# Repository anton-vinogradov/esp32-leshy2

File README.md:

<div align="center">

# Leshy2 ⭐

### An open standalone pocket tool for radio, communication and authorised research

**2.4/5-GHz Wi‑Fi · BLE · 802.15.4 · 3× nRF24 · Sub‑GHz · VHF/UHF · FM/AM/SW/LW/Airband · IR · LoRa/CC1101+NFC Cap**

[Capabilities](docs/hardware.md) · [Roadmap](docs/roadmap.md) · [Stage reports](docs/stage-results.md) · [Schematics](docs/schematics.md) · [Firmware](https://github.com/anton-vinogradov/esp32-leshy2-firmware) · [Русский](README.ru.md)

</div>

<!-- current-substep: H6.0.3-R1 -->

## What we want

Leshy2 is intended to be a hobby device combining spectrum
observation, communication, diagnostics and safe experimentation without a
mandatory laptop. The first order targets one genuinely working prototype:
the factory supplies two populated PCBAs and the owner completes a simple,
solder-free final assembly.

Repairability is not a design priority and does not justify greater cost, size,
or layout/manufacturing complexity. Optional service conveniences are acceptable
only without those penalties. Safety, reliability, required assembly and test
access, and firmware programming/recovery remain mandatory.

PCB layer count is an engineering choice based on electrical integrity,
manufacturability and the complete quoted cost, not a minimization target.
The current six-layer baseline is retained until a validated comparison justifies a change.

| Area | Intended result |
|---|---|
| Radio | S3 Wi‑Fi/BLE, C5 2.4/5-GHz Wi‑Fi and 802.15.4, 3× full nRF24, CC1101, VHF/UHF voice, FM/AM/SW/LW/Airband RX and IR |
| Interface | 3.5-inch 320×480 touch IPS, direct i8080‑8, buttons, encoder, microSD and audio |
| Expansion | Protected Cap slot for U214 LoRa or U219 CC1101+NFC and an M5 Unit port |
| Reliability | Four independent USB ports, accessible recovery, hardware TX evidence and fail-closed safety |

Transmission and hazardous laboratory functions are constrained by the
[safety model](docs/safety.md); the device is only for lawful use with the
system owner's permission.

## What we decided

- Two 80 × 150-mm six-layer boards: front UI/radio and rear RF/power.
- Six compute domains: S3, C5, front Hub RP, rear RF RP, Pack and Safety.
- Ten permanent antenna ports are split 5+5; each RF path remains board-local and reaches its external connector directly or through one removable microcoax.
- The EastRising `ER-TFT035IPS-6 + ER-TPC035-6` display connects directly to S3 through a 50-contact ZIF and i8080‑8; its FPC points toward the antenna edge, folds without twist and retains at least 5 mm of relaxed reserve.
- The factory fabricates and populates two PCBAs. Without soldering, the owner fits the display on a stock rectangular PSA pad, five microcoax jumpers, knob, fasteners and enclosure.
- The 80-contact M1 carries no structural load; four nylon screws, compression stops and the enclosure carry it.
- The 80 × 150-mm outline remains while routing meets its rules. If a required power, USB/i8080 or RF path cannot route after legal local rearrangement, the next candidate is 85 × 150 mm followed by complete requalification.

## What is designed

### Physical layout

The current preview below is composed from the actual PCBs: exterior faces share one scale, without an extra rear-board mirror. Only the installed display panel's envelope is added in blue. This is not an assembled 3D validation. Inspect the inner sides in [all four current component views](docs/h6-r2-component-views.md). Coordinates and cable paths are available in the [exact-placement](docs/h6-r2-exact-placement.md) and [microcoax](docs/h6-r2-microcoax-service.md) views.

H1-to-native correspondence is not fully verified: H1 remains a concept archive, not a picture of current positions. [H6 corrections and open interface findings](docs/h6-r2-interface-review.md) describe the current boards.

[Placement corrections and their verification](docs/h6-r2-placement-repair.md) explain the holder, encoder, port/card access and internal audio assembly. The routing phase is still open.

[Component unification](docs/h6-r2-component-unification.md): GCT USB4105-GF-A ×4 is installed on the native boards; fresh DRC/parity and preservation checks pass. Other candidates and necessary functional differences remain separate.

[Archive: H1 concept four-face Leshy2 mock-up](docs/images/h1-r2-four-faces.svg?rev=h1-r2.39-views-20260907)

[Legend for 223 H1 concept bodies](docs/images/h1-r2-component-legend.svg?rev=h1-r2.39-views-20260907) ·
[physical-design report](docs/h1-r2-physical-layout.md) ·
[functional-architecture report](docs/h0-r2-functional-architecture.md) ·
[front inner face](docs/images/h1-r2-inner-ui.svg) ·
[rear inner face](docs/images/h1-r2-inner-rf.svg) ·
[display mounting](docs/images/display-mount.svg) ·
[physical sections](docs/images/h1-r2-inner-sections.svg)

### Current routing

These are exports from the live `.kicad_pcb` files, not illustrative mock-ups.
Open either board for the full-size SVG.

<table>
  <tr>
    <td width="50%"></td>
    <td width="50%"></td>
  </tr>
  <tr><td align="center">UI PCB</td><td align="center">RF / power PCB</td></tr>
</table>

### Current components · both faces

All four views use the same scale. Outer faces are above; inner faces below
are viewed after turning each board over, with the antenna edge still at the top.
Grey shows component outlines/references; blue is actual silkscreen.
Known footprint defects remain visible — these views do not certify assembly.
[Full-size views and legend](docs/h6-r2-component-views.md). Gold shows all 50 SMA lands and the two-sided copper lands of USB, Cap and encoder interfaces; NFC endpoints are distinguished in the legend.

[Interface labels and coverage](docs/h6-r2-interface-silkscreen.md) distinguish user, service and assembly silkscreen from grey drawing references.

<table>
  <tr><th width="50%">Front / UI</th><th width="50%">Rear / RF-power</th></tr>
  <tr>
    <td></td>
    <td></td>
  </tr>
  <tr>
    <td></td>
    <td></td>
  </tr>
</table>

Component views refresh together with routing exports; the common freshness
check rejects images that no longer match the PCB files.

## What we obtained and verified

**Current hardware marker: `H6.0.3-R1`.**

- The historical H0–H5 reviews, including H2 native production ECAD, retain their own baseline scope; their reports are collected in [one index](docs/stage-results.md).
- **Current H3 is `review_required`.** The [current analytical result](docs/h3-r2-acceptance.md) and [rail-voltage paths](docs/power-rail-margins.md) now use the fitted MAIN converter/divider/current-setting resistor. They expose current and voltage shortfalls; MAIN temperature is not established. The MAIN/AON circuit remains unqualified for production or battery energization.
- Both native KiCad boards pass the current [exact-placement checks](docs/h6-r2-exact-placement.md).
- Manufacturer-drawing corrections are being integrated into both PCBs. The [native interface review](docs/h6-r2-interface-review.md) separates applied corrections from remaining assembly gates; clean DRC alone does not prove physical assembly.
- Recovery: S3 ROM UART0 has dedicated native pins; the [C5 TS3/LV control correction](docs/h6-r2-c5-mux-control-review.md) is implemented in source/native ECAD with scoped topology and DRC/parity checks passed. The Safety service manager, electrical/HIL qualification and KILL/update policy remain open; LV20 requires Pre-order, MOQ 21. [Actual recovery boundary](docs/service-recovery.md).
- [Routing automation and design checks](docs/h6-r2-routing-automation.md): the benchmark passed **474/474 connections plus three identical cold replays per block**; the new parallel acceptance command reports current design blockers explicitly. Production routing remains paused pending full-board and electrical qualification. Live copper/connectivity counts, hash-bound DRC results and electrical-review limitations have one owner: [H6.0.3-R1](docs/h6-r2-current-routing.md).
- Native ERC currently uses passive symbol pins; zero findings do not prove correct rail sources or compatible outputs. This electrical-semantics gap blocks release; [corrected pin mappings and partial typed-ERC review](docs/h6-r2-electrical-semantics.md) describe the current evidence and remaining work.

## What remains

1. Correct the native interface/assembly findings and close the electrical-pin/rail-source review gap, then finish every connection and zero schematic-to-PCB parity in H6.0.3.
2. Re-run power/thermal, USB/i8080/M1, RF/Airband, plane and return-current checks on the actual copper.
3. Check STEP, enclosure, cables and final assembly; produce Gerber/BOM/CPL and complete independent DFM/CPL review.
4. Build the first-spin firmware package: reproducible images, fake HAL, available emulation, display test patterns and a safe first-power-on procedure.
5. Immediately before ordering, recheck every exact MPN against JLCPCB Standard PCBA stock/MOQ/price and approve the single actual quote.

Ordering and fabrication remain blocked.

## How the documentation is organised

Each kind of information now has one owner so the same decision is not retold
on several pages:

| Document | Sole role |
|---|---|
| This page | Product story: intent → decisions → implementation → result → remaining work |
| [Roadmap](docs/roadmap.md) | Stage order, current marker and transition criteria only |
| [Stage reports](docs/stage-results.md) | Links to immutable completed-phase results only |
| [Physical design](docs/h1-r2-physical-layout.md), [schematics](docs/schematics.md), [cost](docs/h1-r2-cost.md) | Detail for one subject area |
| `hardware/**/generated` and release contracts | Machine-checkable truth |

Navigation links may repeat; substantive claims belong to their one owner. The
English pages are translations of the Russian pages with the same structure,
not a second independent narrative.

Licensed under [CERN Open Hardware Licence Version 2 — Strongly Reciprocal](LICENSE).

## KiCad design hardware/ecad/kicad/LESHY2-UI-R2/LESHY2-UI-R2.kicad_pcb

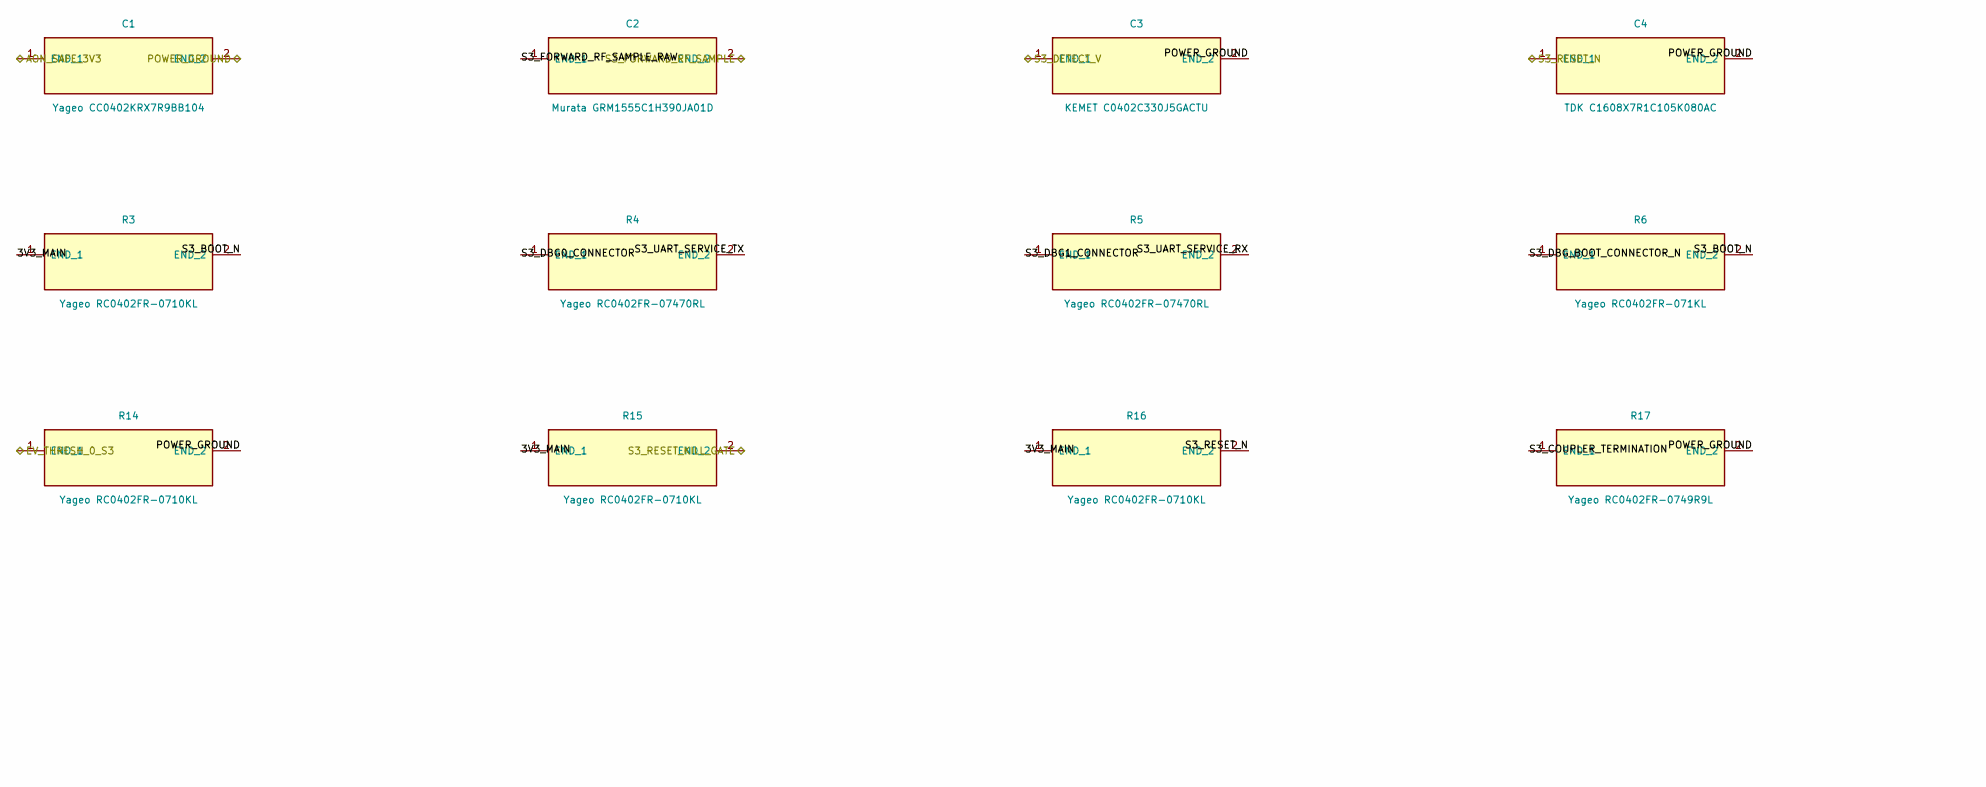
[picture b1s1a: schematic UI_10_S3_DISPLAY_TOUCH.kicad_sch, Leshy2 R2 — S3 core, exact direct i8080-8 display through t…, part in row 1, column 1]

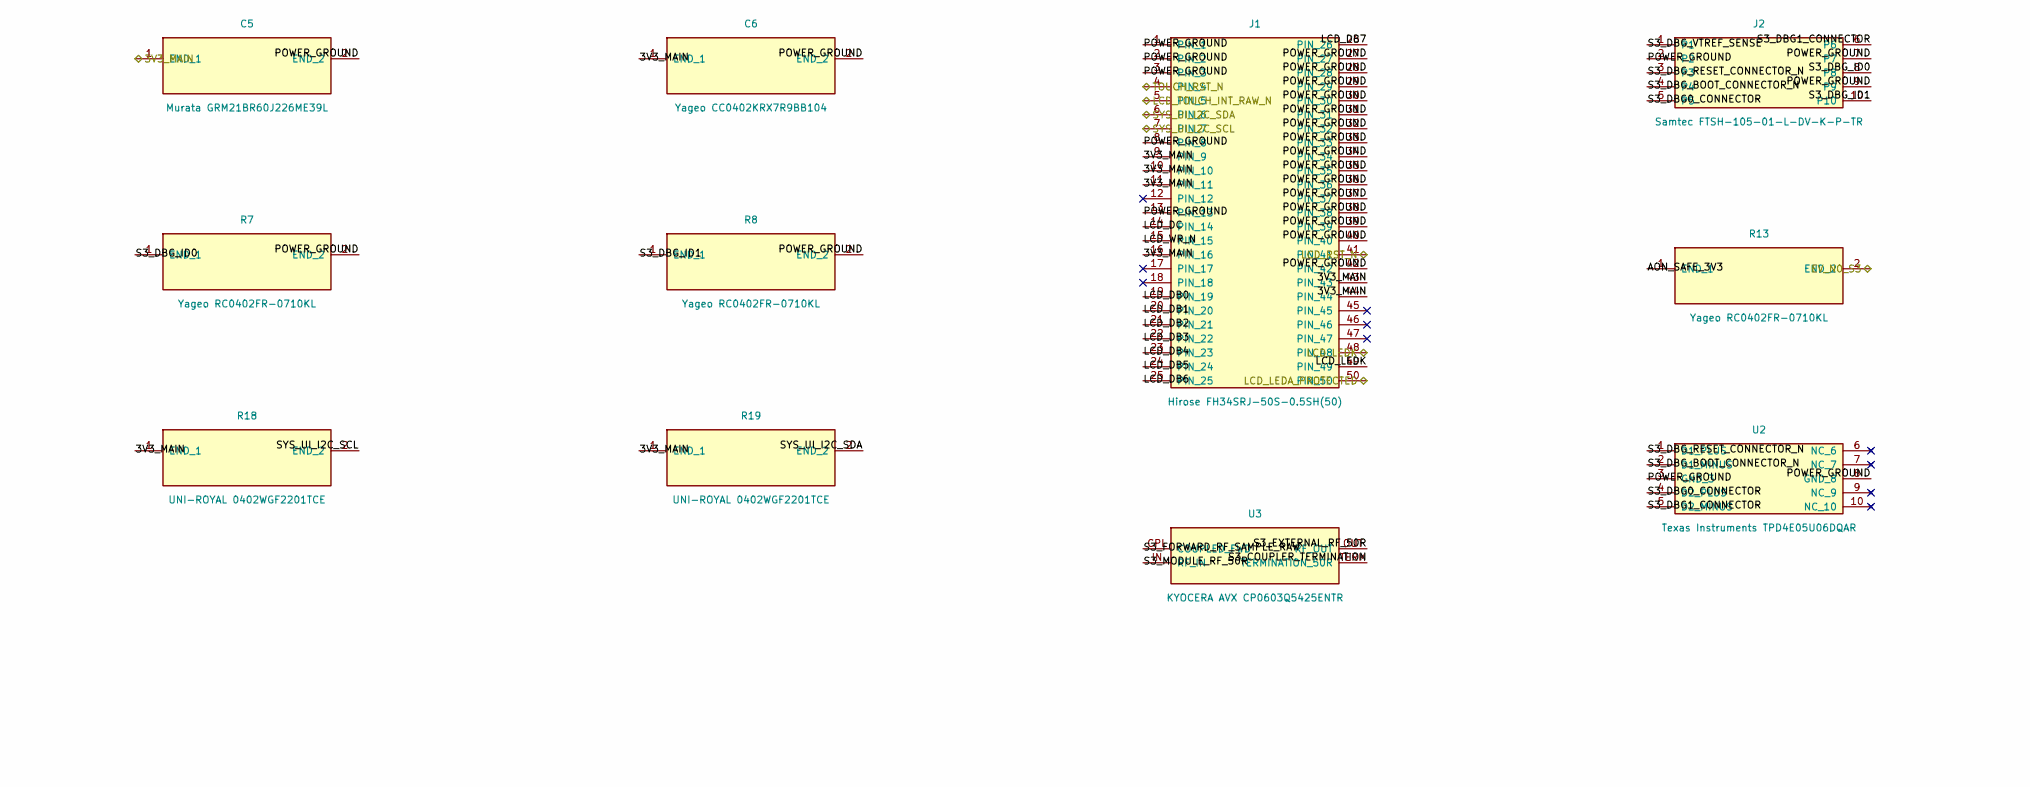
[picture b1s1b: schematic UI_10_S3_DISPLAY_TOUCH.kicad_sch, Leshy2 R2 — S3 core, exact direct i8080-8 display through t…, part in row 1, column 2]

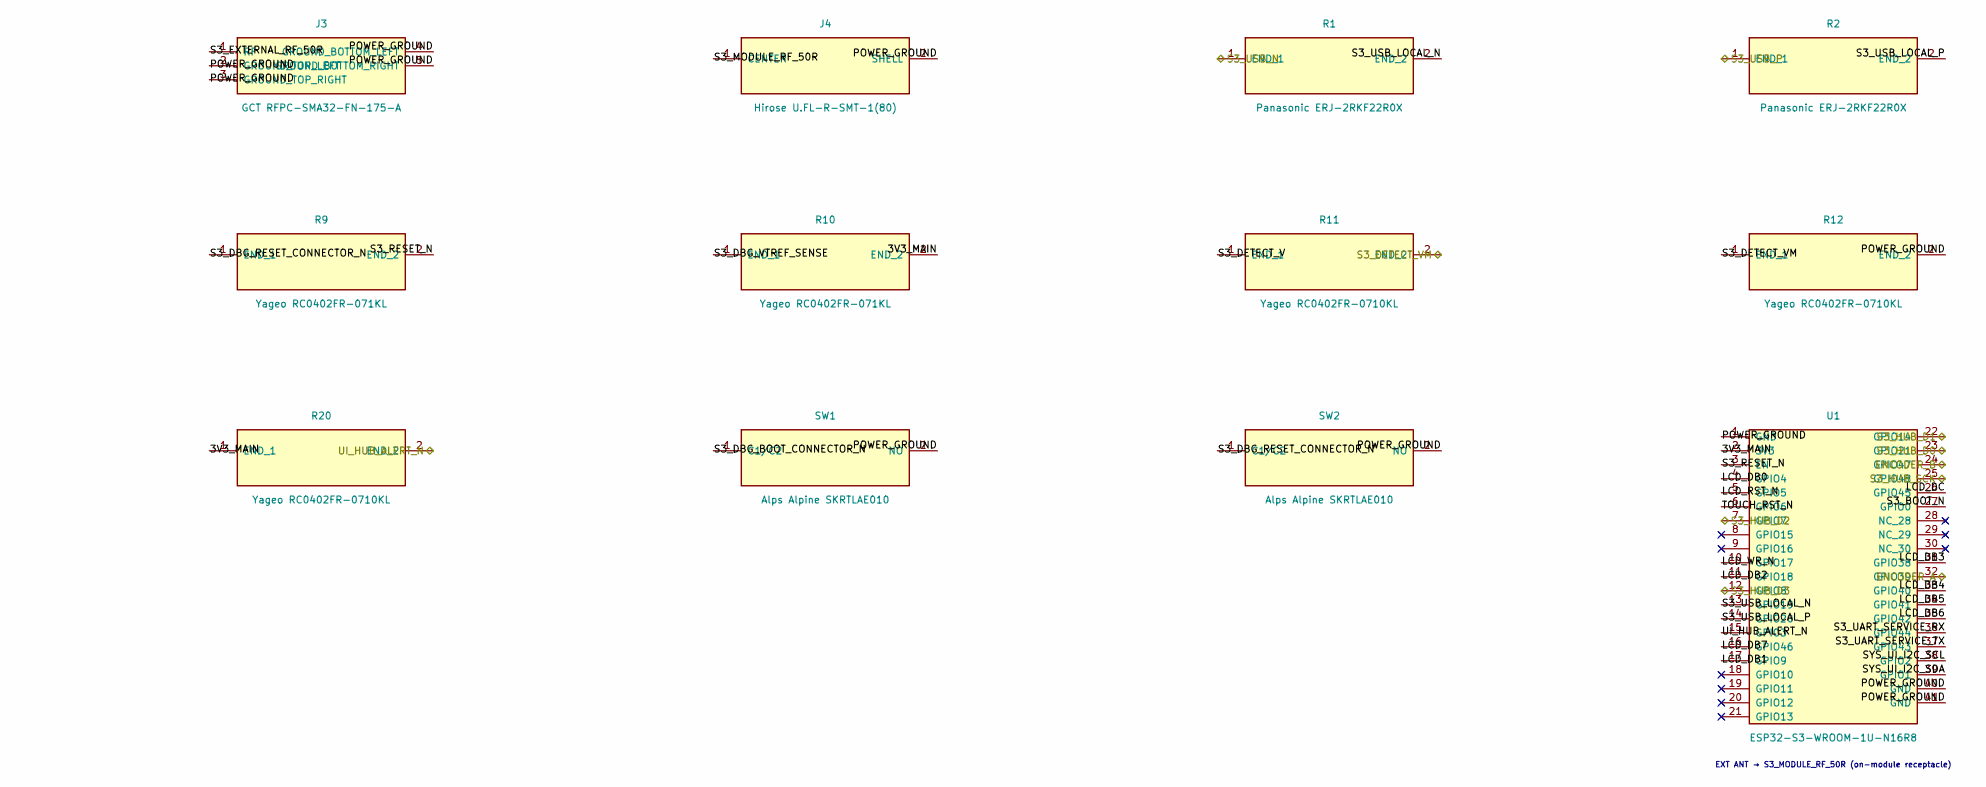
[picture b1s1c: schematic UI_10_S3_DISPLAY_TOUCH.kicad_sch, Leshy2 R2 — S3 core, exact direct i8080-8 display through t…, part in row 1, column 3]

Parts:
C1, C6: Yageo CC0402KRX7R9BB104; C_0402_1005Metric
C2: Murata GRM1555C1H390JA01D; C_0402_1005Metric
C3: KEMET C0402C330J5GACTU; C_0402_1005Metric
C4: TDK C1608X7R1C105K080AC; C_0603_1608Metric
C5: Murata GRM21BR60J226ME39L; C_0805_2012Metric
J1: Hirose FH34SRJ-50S-0.5SH(50); FH34SRJ-50S-0.5SH-50
J2: Samtec FTSH-105-01-L-DV-K-P-TR; FTSH-105-01-L-DV-K-P-TR
J3: GCT RFPC-SMA32-FN-175-A; RFPC-SMA32-FN-175-A
J4: Hirose U.FL-R-SMT-1(80); U.FL_Hirose_U.FL-R-SMT-1_Vertical
R1, R2: Panasonic ERJ-2RKF22R0X; R_0402_1005Metric
R3, R7, R8, R11, R12, R13, R14, R15, R16, R20: Yageo RC0402FR-0710KL; R_0402_1005Metric
R4, R5: Yageo RC0402FR-07470RL; R_0402_1005Metric
R6, R9, R10: Yageo RC0402FR-071KL; R_0402_1005Metric
R17: Yageo RC0402FR-0749R9L; R_0402_1005Metric
R18, R19: UNI-ROYAL 0402WGF2201TCE; R_0402_1005Metric
SW1, SW2: Alps Alpine SKRTLAE010; SW_Push_1P1T-MP_NO_Horizontal_Alps_SKRTLAE010
U1: ESP32-S3-WROOM-1U-N16R8; ESP32-S3-WROOM-1U
U2: Texas Instruments TPD4E05U06DQAR; USON-10_2.5x1.0mm_P0.5mm
U3: KYOCERA AVX CP0603Q5425ENTR; CP0603Q5425ENTR

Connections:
/UI_10_S3_DISPLAY_TOUCH/3V3_MAIN: C5.1 (END_1), C6.1 (END_1), J1.9 (PIN_9), J1.10 (PIN_10), J1.11 (PIN_11), J1.16 (PIN_16), J1.43 (PIN_43), J1.44 (PIN_44), R3.1 (END_1), R10.2 (END_2), R15.1 (END_1), R16.1 (END_1), R18.1 (END_1), R19.1 (END_1), R20.1 (END_1), U1.2 (3V3); also elsewhere on the board
/UI_10_S3_DISPLAY_TOUCH/AON_SAFE_3V3: C1.1 (END_1), R13.1 (END_1); also elsewhere on the board
/UI_10_S3_DISPLAY_TOUCH/ENCODER_A: U1.32 (GPIO39); also elsewhere on the board
/UI_10_S3_DISPLAY_TOUCH/ENCODER_B: U1.24 (GPIO47); also elsewhere on the board
/UI_10_S3_DISPLAY_TOUCH/LCD_DB0: J1.19 (PIN_19), U1.4 (GPIO4)
/UI_10_S3_DISPLAY_TOUCH/LCD_DB1: J1.20 (PIN_20), U1.17 (GPIO9)
/UI_10_S3_DISPLAY_TOUCH/LCD_DB2: J1.21 (PIN_21), U1.11 (GPIO18)
/UI_10_S3_DISPLAY_TOUCH/LCD_DB3: J1.22 (PIN_22), U1.31 (GPIO38)
/UI_10_S3_DISPLAY_TOUCH/LCD_DB4: J1.23 (PIN_23), U1.33 (GPIO40)
/UI_10_S3_DISPLAY_TOUCH/LCD_DB5: J1.24 (PIN_24), U1.34 (GPIO41)
/UI_10_S3_DISPLAY_TOUCH/LCD_DB6: J1.25 (PIN_25), U1.35 (GPIO42)
/UI_10_S3_DISPLAY_TOUCH/LCD_DB7: J1.26 (PIN_26), U1.16 (GPIO46)
/UI_10_S3_DISPLAY_TOUCH/LCD_DC: J1.14 (PIN_14), U1.26 (GPIO45)
/UI_10_S3_DISPLAY_TOUCH/LCD_LEDK: J1.48 (PIN_48), J1.49 (PIN_49); also elsewhere on the board
/UI_10_S3_DISPLAY_TOUCH/LCD_RST_N: J1.41 (PIN_41), U1.5 (GPIO5); also elsewhere on the board
/UI_10_S3_DISPLAY_TOUCH/LCD_WR_N: J1.15 (PIN_15), U1.10 (GPIO17)
/UI_10_S3_DISPLAY_TOUCH/POWER_GROUND: C1.2 (END_2), C3.2 (END_2), C4.2 (END_2), C5.2 (END_2), C6.2 (END_2), J1.1 (PIN_1), J1.2 (PIN_2), J1.3 (PIN_3), J1.8 (PIN_8), J1.13 (PIN_13), J1.27 (PIN_27), J1.28 (PIN_28), J1.29 (PIN_29), J1.30 (PIN_30), J1.31 (PIN_31), J1.32 (PIN_32), J1.33 (PIN_33), J1.34 (PIN_34), J1.35 (PIN_35), J1.36 (PIN_36), J1.37 (PIN_37), J1.38 (PIN_38), J1.39 (PIN_39), J1.40 (PIN_40), J1.42 (PIN_42), J2.2, J2.7, J2.9, J3.2 (GROUND_TOP_LEFT), J3.3 (GROUND_TOP_RIGHT), J3.4 (GROUND_BOTTOM_LEFT), J3.5 (GROUND_BOTTOM_RIGHT), J4.2 (SHELL), R7.2 (END_2), R8.2 (END_2), R12.2 (END_2), R14.2 (END_2), R17.2 (END_2), SW1.2 (NO), SW2.2 (NO), U1.1 (GND), U1.40 (GND), U1.41 (GND), U2.3 (GND_3), U2.8 (GND_8); also elsewhere on the board
/UI_10_S3_DISPLAY_TOUCH/S3_BOOT_N: R3.2 (END_2), R6.2 (END_2), U1.27 (GPIO0)
/UI_10_S3_DISPLAY_TOUCH/S3_COUPLER_TERMINATION: R17.1 (END_1), U3.TERM (TERMINATION_50R)
/UI_10_S3_DISPLAY_TOUCH/S3_DBG0_CONNECTOR: J2.5, R4.1 (END_1), U2.4 (D2_PLUS)
/UI_10_S3_DISPLAY_TOUCH/S3_DBG1_CONNECTOR: J2.6, R5.1 (END_1), U2.5 (D2_MINUS)
/UI_10_S3_DISPLAY_TOUCH/S3_DBG_BOOT_CONNECTOR_N: J2.4, R6.1 (END_1), SW1.1 (C1/C2), U2.2 (D1_MINUS)
/UI_10_S3_DISPLAY_TOUCH/S3_DBG_ID0: J2.8, R7.1 (END_1)
/UI_10_S3_DISPLAY_TOUCH/S3_DBG_ID1: J2.10, R8.1 (END_1)
/UI_10_S3_DISPLAY_TOUCH/S3_DBG_RESET_CONNECTOR_N: J2.3, R9.1 (END_1), SW2.1 (C1/C2), U2.1 (D1_PLUS)
/UI_10_S3_DISPLAY_TOUCH/S3_DBG_VTREF_SENSE: J2.1, R10.1 (END_1)
/UI_10_S3_DISPLAY_TOUCH/S3_DETECT_V: C3.1 (END_1), R11.1 (END_1); also elsewhere on the board
/UI_10_S3_DISPLAY_TOUCH/S3_DETECT_VM: R11.2 (END_2), R12.1 (END_1); also elsewhere on the board
/UI_10_S3_DISPLAY_TOUCH/S3_EXTERNAL_RF_50R: J3.1 (RF), U3.OUT (RF_OUT)
/UI_10_S3_DISPLAY_TOUCH/S3_FORWARD_RF_SAMPLE: C2.2 (END_2); also elsewhere on the board
/UI_10_S3_DISPLAY_TOUCH/S3_FORWARD_RF_SAMPLE_RAW: C2.1 (END_1), U3.CPL (COUPLED_FWD)
/UI_10_S3_DISPLAY_TOUCH/S3_HUB_D0: U1.23 (GPIO21); also elsewhere on the board
/UI_10_S3_DISPLAY_TOUCH/S3_HUB_D1: U1.22 (GPIO14); also elsewhere on the board
/UI_10_S3_DISPLAY_TOUCH/S3_HUB_D2: U1.7 (GPIO7); also elsewhere on the board
/UI_10_S3_DISPLAY_TOUCH/S3_HUB_D3: U1.12 (GPIO8); also elsewhere on the board
/UI_10_S3_DISPLAY_TOUCH/S3_HUB_SCK: U1.25 (GPIO48); also elsewhere on the board
/UI_10_S3_DISPLAY_TOUCH/S3_MODULE_RF_50R: J4.1 (CENTER), U3.IN (RF_IN)
/UI_10_S3_DISPLAY_TOUCH/S3_RESET_KILL_GATE: R15.2 (END_2); also elsewhere on the board
/UI_10_S3_DISPLAY_TOUCH/S3_RESET_N: C4.1 (END_1), R9.2 (END_2), R16.2 (END_2), U1.3 (EN); also elsewhere on the board
/UI_10_S3_DISPLAY_TOUCH/S3_UART_SERVICE_RX: R5.2 (END_2), U1.36 (GPIO44)
/UI_10_S3_DISPLAY_TOUCH/S3_UART_SERVICE_TX: R4.2 (END_2), U1.37 (GPIO43)
/UI_10_S3_DISPLAY_TOUCH/S3_USB_LOCAL_N: R1.2 (END_2), U1.13 (GPIO19)
/UI_10_S3_DISPLAY_TOUCH/S3_USB_LOCAL_P: R2.2 (END_2), U1.14 (GPIO20)
/UI_10_S3_DISPLAY_TOUCH/S3_USB_N: R1.1 (END_1); also elsewhere on the board
/UI_10_S3_DISPLAY_TOUCH/S3_USB_P: R2.1 (END_1); also elsewhere on the board
/UI_10_S3_DISPLAY_TOUCH/SYS_UI_I2C_SCL: J1.7 (PIN_7), R18.2 (END_2), U1.38 (GPIO2); also elsewhere on the board
/UI_10_S3_DISPLAY_TOUCH/SYS_UI_I2C_SDA: J1.6 (PIN_6), R19.2 (END_2), U1.39 (GPIO1); also elsewhere on the board
/UI_10_S3_DISPLAY_TOUCH/TOUCH_RST_N: J1.4 (PIN_4), U1.6 (GPIO6); also elsewhere on the board
/UI_10_S3_DISPLAY_TOUCH/UI_HUB_ALERT_N: R20.2 (END_2), U1.15 (GPIO3); also elsewhere on the board
/UI_11_STORAGE_CONTROLS_INDICATORS/LCD_LEDA_PROTECTED: J1.50 (PIN_50); also elsewhere on the board
/UI_11_STORAGE_CONTROLS_INDICATORS/LCD_TOUCH_INT_RAW_N: J1.5 (PIN_5); also elsewhere on the board
/UI_50_FRONT_POWER_SAFETY/EV_N0_S3: R13.2 (END_2); also elsewhere on the board
/UI_50_FRONT_POWER_SAFETY/EV_THRESH_0_S3: R14.1 (END_1); also elsewhere on the board

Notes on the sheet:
EXT ANT → S3_MODULE_RF_50R (on-module receptacle)
